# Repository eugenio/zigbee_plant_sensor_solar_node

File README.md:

# Zigbee Plant Sensor Solar Node

Solar-powered environmental monitoring node for outdoor plant care. Measures temperature, humidity, light, soil moisture, and battery state via Zigbee 802.15.4 — integrates with Home Assistant, Zigbee2MQTT, and ZHA.

## Motivation

Commercial plant sensors are either battery-hungry, lack solar charging, or miss key measurements. This node combines an MPPT solar charger with deep-sleep Zigbee to achieve indefinite outdoor operation while reporting six sensor channels.

## Hardware Overview

| Block              | Component          | Function                                |
| ------------------ | ------------------ | --------------------------------------- |
| MCU                | ESP32-C6-MINI-1-N4 | Zigbee 802.15.4 / WiFi / BLE, 4MB flash |
| MPPT Charger       | SPV1040T           | Autonomous solar boost charger, 5W max  |
| LDO                | HT7833             | 3.3V 500mA, 4uA quiescent              |
| Battery Protection | XB3306D            | Overcharge / overdischarge / overcurrent |
| Temp/Humidity      | SHT40              | +/-0.2 degC, +/-1.8% RH (onboard)      |
| Ambient Light      | VEML7700           | 0.0036 - 120k lux                      |
| Fuel Gauge         | MAX17048           | Li-Po SOC estimation, low-battery alert |
| External Temp      | ADS1115 + NTC 10k  | 0.1 degC resolution, metal-tip probe   |
| Expansion          | 2x Qwiic I2C      | Soil moisture, EC sensor                |

**Board**: 60 x 48 mm, 4-layer, 1.6mm FR4

## Quick Start

```bash
# 1. Install atopile
pip install atopile

# 2. Clone and build
git clone <repo-url> && cd zigbee_plant_sensor_solar_node
ato build

# 3. Open PCB in KiCad
kicad layouts/default/default.kicad_pcb
```

## Project Structure

```text
.
├── main.ato                    # Top-level schematic (App module)
├── micromppt.ato               # MPPT solar charger (SPV1040T)
├── ldo.ato                     # 3.3V LDO (HT7833)
├── loadswitch.ato              # P-FET high-side load switch (SI2301CDS)
├── ntc_adc.ato                 # External NTC thermistor (ADS1115)
├── xiao_esp32c6.ato            # ESP32-C6 MCU driver
├── ato.yaml                    # Atopile project config + dependencies
├── pixi.toml                   # Pixi environment config
├── parts/                      # Component packages (32 parts, 4 files each)
│   ├── Texas_Instruments_ADS1115IRUGR/   # .ato + .kicad_mod + .kicad_sym + .step
│   ├── STMicroelectronics_SPV1040T/
│   ├── Espressif_Systems_ESP32_C6_MINI_1_N4/
│   └── ...                     # Resistors, caps, connectors, ICs
├── layouts/default/            # KiCad PCB layout (60x48mm, 4-layer)
│   ├── default.kicad_pcb
│   ├── default.kicad_sch
│   └── default.kicad_pro
├── docs/
│   ├── pcb_placement_strategy.md
│   ├── power_budget.md
│   ├── uml/architecture.puml  # System block diagram
│   └── adr/ADR-001-external-ntc-thermistor.md
└── scripts/
    └── place_components.py     # Automated PCB placement

176 tracked files. Atopile dependencies (sensirion-sht40, vishay-veml7700,
maxim-max17048, sparkfun-qwiic) are gitignored and reinstalled by `ato build`.
```

## Power Budget

| Mode               | Current    | Duration       | Notes                      |
| ------------------ | ---------- | -------------- | -------------------------- |
| Deep Sleep         | ~82 uA     | 99% of time    | Fuel gauge + LDO quiescent |
| Active (sense + TX)| ~120 mA    | ~500 ms        | Zigbee transmit burst      |
| Solar input        | 200-400 mA | Daylight hours | 5V / 1W panel via MPPT     |

See [docs/power_budget.md](docs/power_budget.md) for detailed analysis.

## Architecture

See [docs/uml/architecture.puml](docs/uml/architecture.puml) for the system block diagram.

## License

MIT

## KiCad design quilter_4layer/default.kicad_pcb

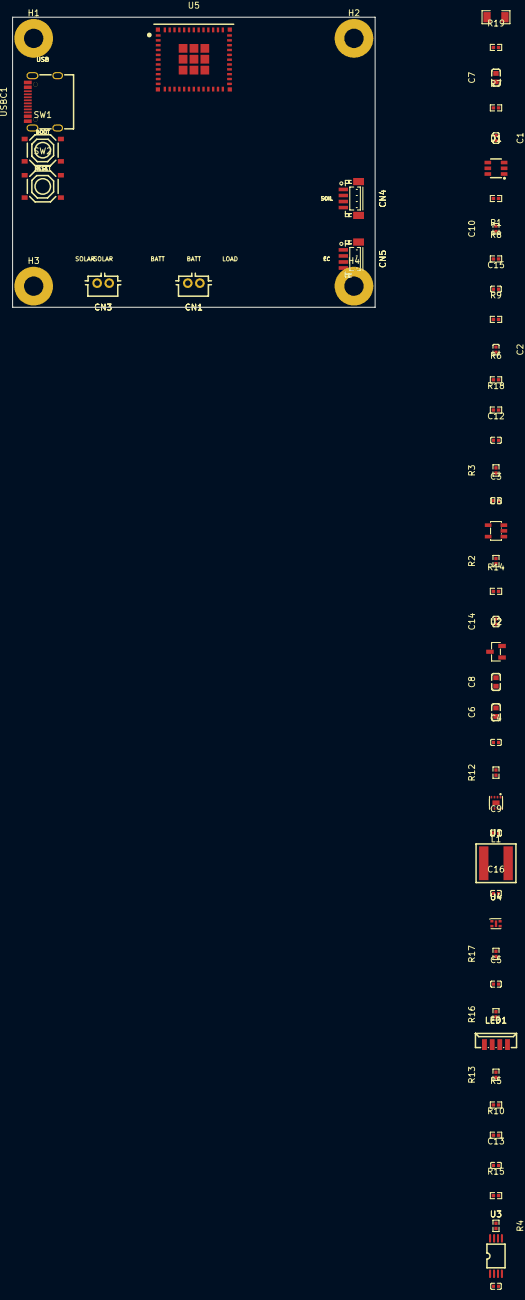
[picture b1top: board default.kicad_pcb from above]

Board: 4 copper layers, 60.0 x 48.0 mm, 55 parts (0 on the bottom side), 23 nets, no tracks yet.

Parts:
C1, C2, C3, C4, C5, C9, C10, C11, C12, C13, C14, C15, C16: 0F; C0402
C6, C7, C8: 0F; C0603
CN1, CN3: CONN-TH_B2B-PH-K-S
CN4, CN5: CONN-SMD_BM04B-SRSS-TB
D1: SOT-23-6_L2.9-W1.6-P0.95-LS2.8-BR
H1, H2, H3, H4: MountingHole_3.2_M3
L1: L ℝ+H; IND-SMD_L6.6-W6.4
LED1: LED-SMD_4P-L6.8-W2.4_VEML7700-TR
R1, R2, R3, R4, R12, R13, R14, R15, R16, R17: 10000Ω; R0402
R5: 1000000Ω; R0402
R6: 450000Ω; R0402
R7, R9, R10: 1000Ω; R0402
R8: 100Ω; R0402
R11: 0.01Ω; R1206
R18, R19: 5100Ω; R0402
SW1, SW2: SW-SMD_4P-L5.1-W5.1-P3.70-LS6.5-TL_H1.5
U1: TDFN-8_L2.0-W2.0-P0.50-BL-EP1.2
U2: SOT-23-3_L2.9-W1.3-P1.90-LS2.4-BR
U3: TSSOP-8_L4.4-W3.0-P0.65-LS6.4-BL
U4: DFN-4_L1.5-W1.5-P0.8-TL-EP
U5: WIFIM-SMD_61P-L16.6-W13.2-P0.80-ESP32-C6-MINI-1-N4
U6: SOT-23-5_L3.0-W1.7-P0.95-LS2.8-BR
USBC1: USB-C_SMD-TYPE-C-31-M-12_1

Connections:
17: U5.17, USBC1.A7, USBC1.B7
18: U5.18, USBC1.A6, USBC1.B6
A: R16.2, SW1.1, SW1.2, U5.23
A5: R18.1, USBC1.A5
B5: R19.1, USBC1.B5
C_bpc-power-hv: C3.1, R8.1, U2.2
Cf-power-hv: C4.1, R9.1, U3.7
Cf-power-lv: C4.2, R10.1, U3.6
Cinsns-power-hv: C5.1, R7.2, U3.1, U3.8
Cout1-power-hv: C7.1, D1.4, D1.5, D1.6, R9.2, R11.1, U3.4
Coutsns-power-hv: C9.1, R5.2, R6.1, U3.5
LX: L1.2, U3.3
QSTRT: R4.1, U1.6
SCL: CN4.4, CN5.4, LED1.1, R2.2, R12.1, R14.2, U1.7, U4.2, U5.16
SDA: CN4.3, CN5.3, LED1.4, R3.2, R13.1, R15.2, U1.8, U4.1, U5.15
Vbatr-hv: C1.1, C8.1, C15.1, CN1.1, R5.1, R8.2, R10.2, R11.2, U1.2, U6.1, U6.3
Vbatr-lv: C3.2, CN1.2, U2.3
Vpvr-hv: C6.1, CN3.1, L1.1, R7.1
c_en-power-hv: C14.1, R17.2, SW2.1, SW2.2, U5.8
hv: C2.1, C10.1, C11.1, C12.1, C13.1, C16.1, CN4.2, CN5.2, LED1.2, R1.2, R2.1, R3.1, R12.2, R13.2, R14.1, R15.1, R16.1, R17.1, U1.3, U4.3, U5.3, U6.5
lv: C1.2, C2.2, C5.2, C6.2, C7.2, C8.2, C9.2, C10.2, C11.2, C12.2, C13.2, C14.2, C15.2, C16.2, CN3.2, CN4.0, CN4.1, CN5.0, CN5.1, D1.1, D1.2, D1.3, LED1.3, R4.2, R6.2, R18.2, R19.2, SW1.3, SW1.4, SW2.3, SW2.4, U1.1, U1.4, U1.9, U2.1, U3.2, U4.4, U4.5, U5.1, U5.2, U5.11, U5.14, U5.36, U5.37, U5.38, U5.39, U5.40, U5.41, U5.42, U5.43, U5.44, U5.45, U5.46, U5.47, U5.48, U5.49, U5.50, U5.51, U5.52, U5.53, U6.2, USBC1.1, USBC1.2, USBC1.3, USBC1.4, USBC1.A1B12, USBC1.B1A12
nALRT: R1.1, U1.5
power_usb-hv: USBC1.A4B9, USBC1.B4A9
